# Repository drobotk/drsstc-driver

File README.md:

# DRSSTC driver

This is a KiCad project of the DRSSTC driver used in my tesla coil.

# Features:
- Single CT input for both clock and overcurrent detection
- Phase lead adjustable with a potentiometer, no need for a tunable inductor
- Adjustable self-oscillation, useful for testing and running a coil at the upper pole frequency
- Traditional / pulse skipping operation selectable with a jumper
- Adjustable UVLO for protecting precious IGBTs
- 74AHC high speed logic, less phase lead needed
- More modern parts than a UD2.7c

# Credits
As with most DRSSTC drivers, this one is based on previous work of many people (Steve Ward, Finn Hammer, Philip Slawinski, Bart Anderson, Eric Goodchild, Gao Guangyan, etc.). The design I took the most inspiration from is [this](https://highvoltageforum.net/index.php?topic=2054.0) project by [Mike](https://highvoltageforum.net/index.php?action=profile;u=1209) on HVF.

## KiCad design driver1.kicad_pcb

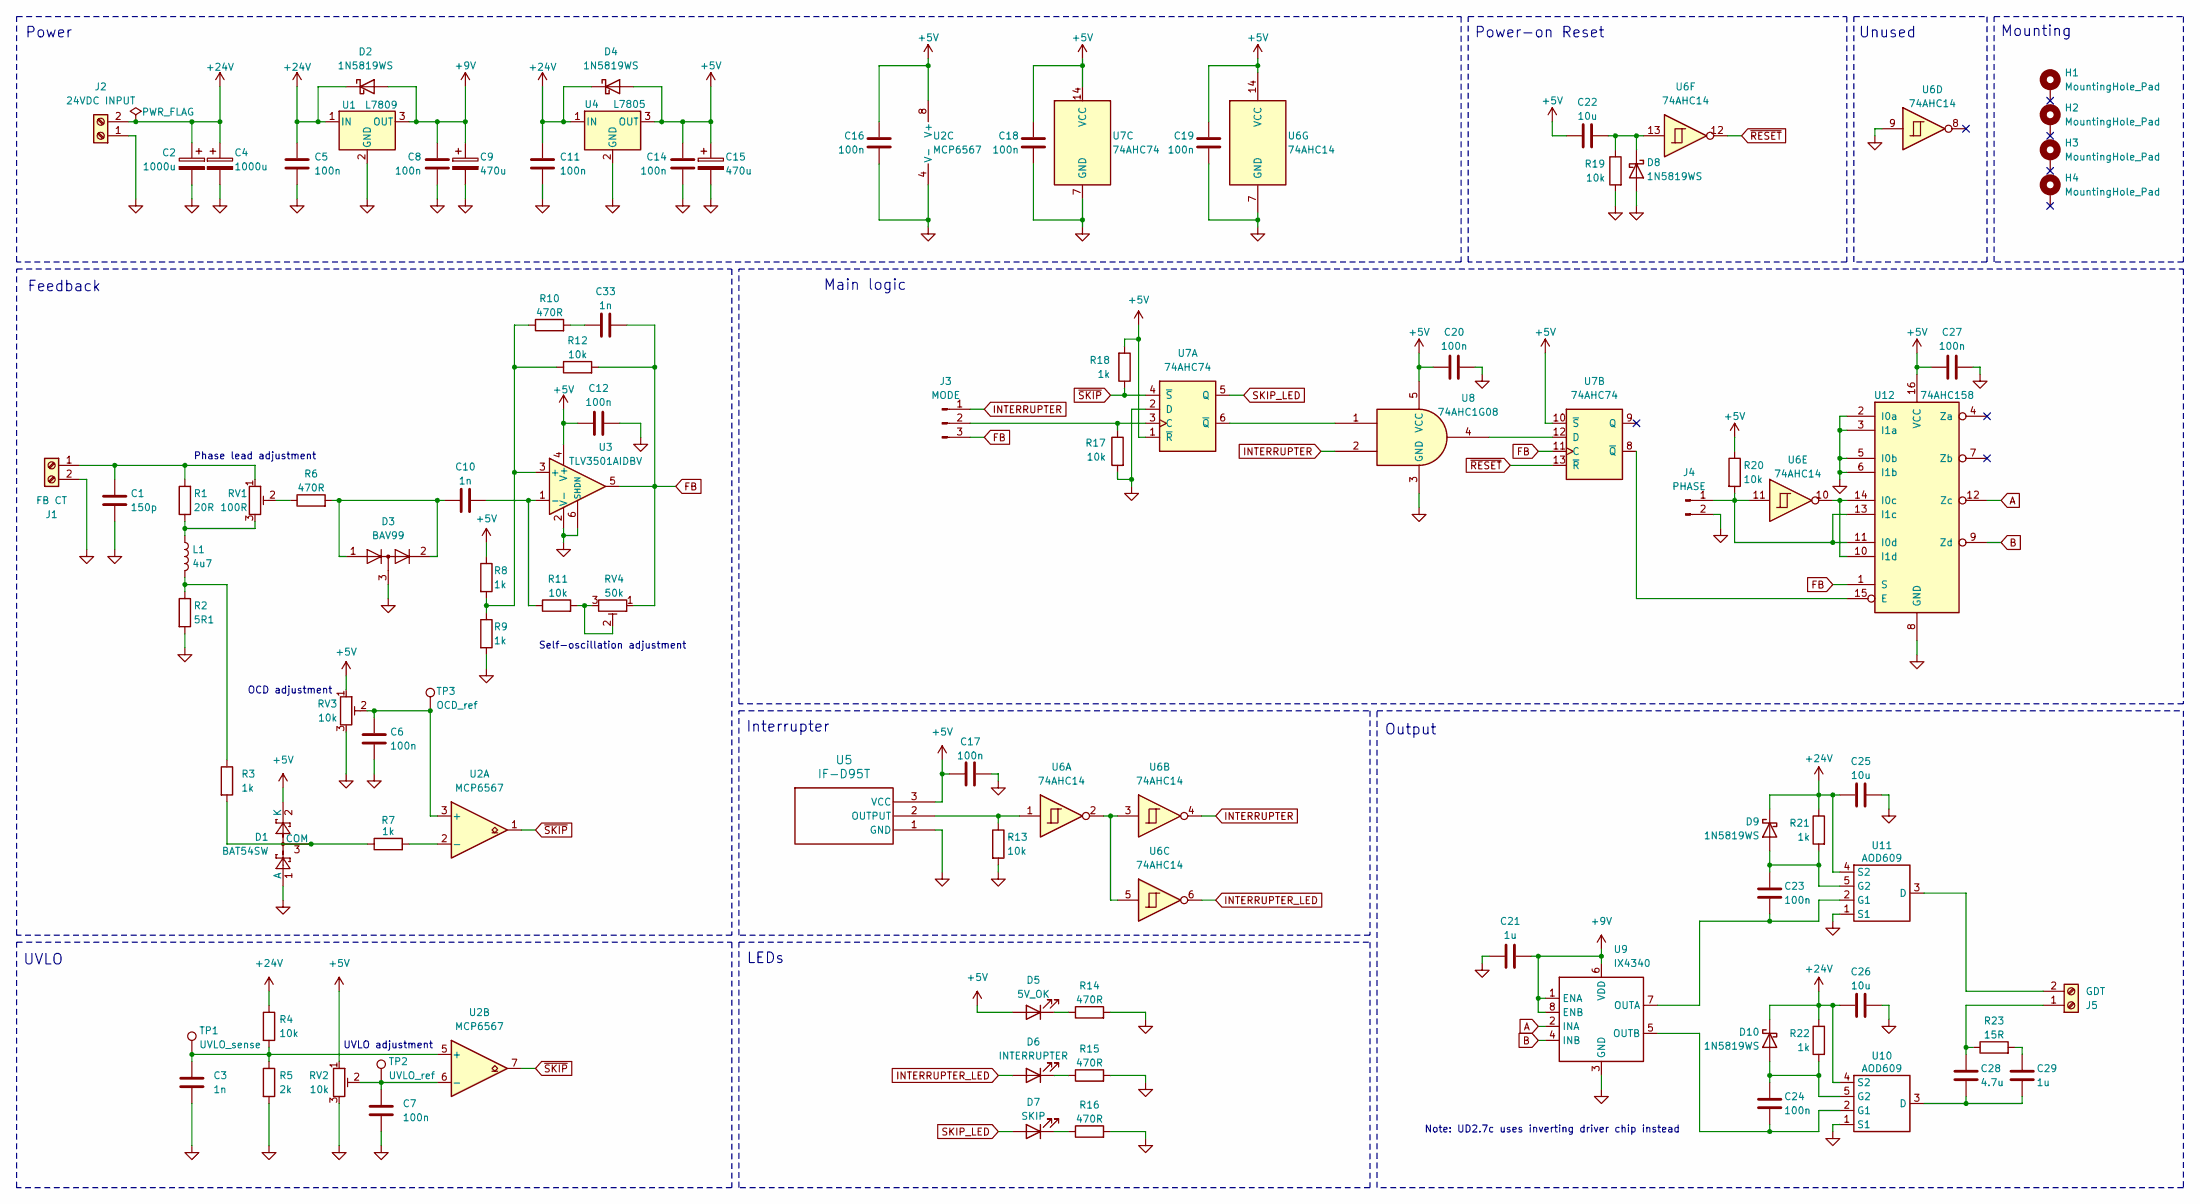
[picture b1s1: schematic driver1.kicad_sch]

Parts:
C1: 150p; C_0603_1608Metric_Pad1.08x0.95mm_HandSolder
C2, C4: 1000u; CP_Radial_D12.5mm_P5.00mm
C3, C10, C33: 1n; C_0603_1608Metric_Pad1.08x0.95mm_HandSolder
C5, C6, C7, C8, C11, C12, C14, C16, C17, C18, C19, C20, C27: 100n; C_0603_1608Metric_Pad1.08x0.95mm_HandSolder
C9, C15: 470u; CP_Radial_D8.0mm_P3.50mm
C21: 1u; C_0805_2012Metric_Pad1.18x1.45mm_HandSolder
C22, C25, C26: 10u; C_0805_2012Metric_Pad1.18x1.45mm_HandSolder
C23, C24: 100n; C_0805_2012Metric_Pad1.18x1.45mm_HandSolder
C28: 4.7u; C_1210_3225Metric_Pad1.33x2.70mm_HandSolder
C29: 1u; C_1210_3225Metric_Pad1.33x2.70mm_HandSolder
D1: BAT54SW; SOT-323_SC-70
D2, D4, D8, D9, D10: 1N5819WS; D_SOD-323
D3: BAV99; SOT-23
D5: 5V_OK; LED_D3.0mm
D6: INTERRUPTER; LED_D3.0mm
D7: SKIP; LED_D3.0mm
H1, H2, H3, H4: MountingHole_Pad; MountingHole_3.2mm_M3_Pad
J1: FB CT; Altech_AK100_1x02_P5.00mm
J2: 24VDC INPUT; Altech_AK100_1x02_P5.00mm
J3: MODE; PinHeader_1x03_P2.54mm_Vertical
J4: PHASE; PinHeader_1x02_P2.54mm_Vertical
J5: GDT; Altech_AK100_1x02_P5.00mm
L1: 4u7; L_Radial_D7.5mm_P3.50mm_Fastron_07P
R1: 20R; R_2512_6332Metric_Pad1.40x3.35mm_HandSolder
R2: 5R1; R_1210_3225Metric_Pad1.30x2.65mm_HandSolder
R3, R7, R8, R9, R18, R21, R22: 1k; R_0603_1608Metric_Pad0.98x0.95mm_HandSolder
R4, R11, R12, R13, R17, R19, R20: 10k; R_0603_1608Metric_Pad0.98x0.95mm_HandSolder
R5: 2k; R_0603_1608Metric_Pad0.98x0.95mm_HandSolder
R6, R10, R14, R15, R16: 470R; R_0603_1608Metric_Pad0.98x0.95mm_HandSolder
R23: 15R; R_1210_3225Metric_Pad1.30x2.65mm_HandSolder
RV1: 100R; Potentiometer_Bourns_3296W_Vertical
RV2, RV3: 10k; Potentiometer_Bourns_3296W_Vertical
RV4: 50k; Potentiometer_Bourns_3296W_Vertical
TP1: UVLO_sense; TestPoint_Pad_D2.0mm
TP2: UVLO_ref; TestPoint_Pad_D2.0mm
TP3: OCD_ref; TestPoint_Pad_D2.0mm
U1: L7809; TO-252-2
U2: MCP6567; MSOP-8_3x3mm_P0.65mm
U3: TLV3501AIDBV; SOT-23-6
U4: L7805; TO-252-2
U5: IF-D95T; IF-D95T_IFB
U6: 74AHC14; TSSOP-14_4.4x5mm_P0.65mm
U7: 74AHC74; TSSOP-14_4.4x5mm_P0.65mm
U8: 74AHC1G08; SOT-353_SC-70-5
U9: IX4340; SOIC-8_3.9x4.9mm_P1.27mm
U10, U11: AOD609; TO-252-4
U12: 74AHC158; TSSOP-16_4.4x5mm_P0.65mm

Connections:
+5V: C12.2, C14.1, C15.1, C16.2, C17.1, C18.2, C19.2, C20.1, C22.1, C27.1, D1.2 (K), D4.2 (A), D5.2 (A), R8.1, R18.2, R20.1, RV2.1, RV3.1, U2.8 (V+), U3.4 (V+), U4.3 (OUT), U5.3 (VCC), U6.14 (VCC), U7.1 (~R), U7.10 (~S), U7.14 (VCC), U8.5 (VCC), U12.16 (VCC)
+9V: C8.1, C9.1, C21.2, D2.2 (A), U1.3 (OUT), U9.1 (ENA), U9.6 (VDD), U9.8 (ENB)
+24V: C2.1, C4.1, C5.1, C11.1, C25.1, C26.1, D2.1 (K), D4.1 (K), D9.1 (K), D10.1 (K), J2.2, R4.1, R21.1, R22.1, U1.1 (IN), U4.1 (IN), U10.4 (S2), U11.4 (S2)
A: U9.2 (INA), U12.12 (Zc)
B: U9.4 (INB), U12.9 (Zd)
FB: C33.2, J3.3, R12.2, RV4.1, U3.5, U7.11 (C), U12.1 (S)
GND: C1.2, C2.2, C3.2, C4.2, C5.2, C6.2, C7.2, C8.2, C9.2, C11.2, C12.1, C14.2, C15.2, C16.1, C17.2, C18.1, C19.1, C20.2, C21.1, C25.2, C26.2, C27.2, D1.1 (A), D3.3 (K), D8.2 (A), J1.2, J2.1, J4.2, R2.2, R5.2, R9.2, R13.2, R14.2, R15.2, R16.2, R17.2, R19.2, RV2.3, RV3.3, U1.2 (GND), U2.4 (V-), U3.2 (V-), U3.6 (SHDN), U4.2 (GND), U5.1 (GND), U6.7 (GND), U6.9, U7.2 (D), U7.7 (GND), U8.3 (GND), U9.3 (GND), U10.1 (S1), U11.1 (S1), U12.2 (I0a), U12.3 (I1a), U12.5 (I0b), U12.6 (I1b), U12.8 (GND)
INTERRUPTER: J3.1, U6.4, U8.2
INTERRUPTER_LED: D6.2 (A), U6.6
unnamed: C29.1, R23.2
unnamed: C33.1, R10.2
unnamed: D1.3 (COM), R3.2, R7.1
unnamed: C10.1, D3.1 (K), D3.2 (A), R6.2
unnamed: D5.1 (K), R14.1
unnamed: D6.1 (K), R15.1
unnamed: D7.1 (K), R16.1
unnamed: C22.2, D8.1 (K), R19.1, U6.13
unnamed: C23.1, D9.2 (A), R21.2, U11.5 (G2)
unnamed: C24.1, D10.2 (A), R22.2, U10.5 (G2)
unnamed: C1.1, J1.1, R1.2, RV1.1
unnamed: J3.2, R17.1, U7.3 (C)
unnamed: J4.1, R20.2, U6.11, U12.11 (I0d), U12.13 (I1c)
unnamed: C28.1, J5.1, R23.1
unnamed: J5.2, U11.3 (D)
unnamed: L1.1, R1.1, RV1.3
unnamed: L1.2, R2.1, R3.1
unnamed: R6.1, RV1.2
unnamed: R11.2, RV4.2, RV4.3
unnamed: C6.1, RV3.2, TP3.1 (1_1), U2.3 (+)
unnamed: R7.2, U2.2 (-)
unnamed: C3.1, R4.2, R5.1, TP1.1 (1_1), U2.5 (+)
unnamed: C7.1, RV2.2, TP2.1 (1_1), U2.6 (-)
unnamed: R8.2, R9.1, R10.1, R12.1, U3.3 (+)
unnamed: C10.2, R11.1, U3.1 (-)
unnamed: R13.1, U5.2 (OUTPUT), U6.1
unnamed: U6.2, U6.3, U6.5
unnamed: U7.6 (~Q), U8.1
unnamed: U7.12 (D), U8.4
unnamed: C28.2, C29.2, U10.3 (D)
unnamed: C24.2, U9.5 (OUTB), U10.2 (G1)
unnamed: C23.2, U9.7 (OUTA), U11.2 (G1)
unnamed: U7.8 (~Q), U12.15 (E)
unnamed: U6.10, U12.10 (I1d), U12.14 (I0c)
SKIP_LED: D7.2 (A), U7.5 (Q)
~RESET: U6.12, U7.13 (~R)
~SKIP: R18.1, U2.1, U2.7, U7.4 (~S)

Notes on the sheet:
Interrupter
Self-oscillation adjustment
Power
Unused
OCD adjustment
UVLO adjustment
UVLO
Power-on Reset
LEDs
Main logic
Phase lead adjustment
Note: UD2.7c uses inverting driver chip instead
Output
Feedback
Mounting

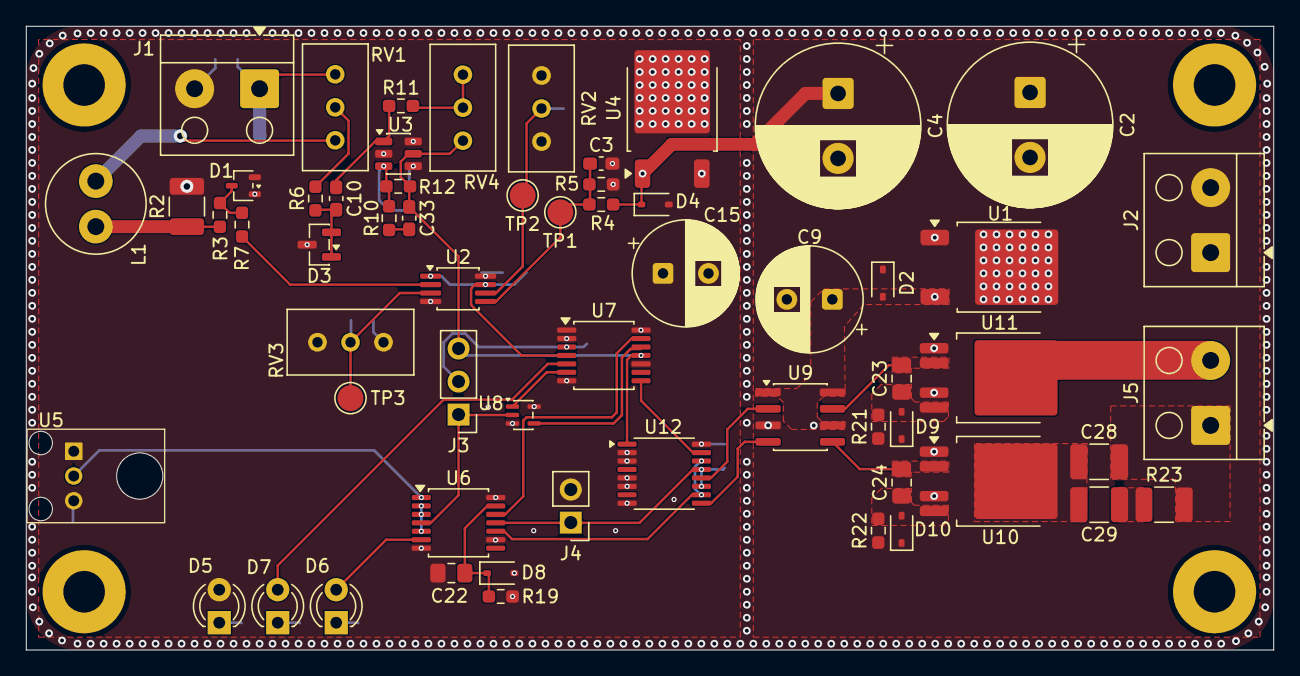
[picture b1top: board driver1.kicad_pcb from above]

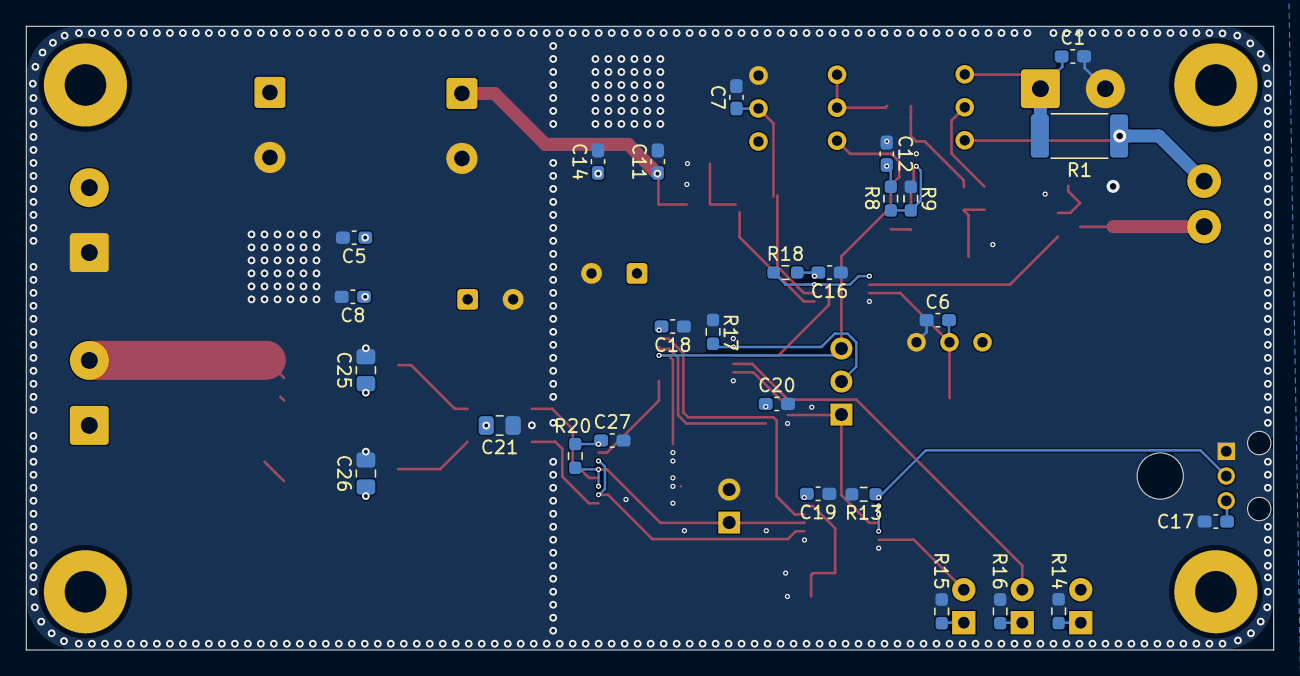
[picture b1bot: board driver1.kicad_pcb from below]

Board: 2 copper layers, 96.0 x 48.0 mm, 91 parts (27 on the bottom side), 46 nets.

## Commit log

2026-03-27 Create LICENSE
2026-03-27 Fix footprint link
2026-03-30 Progress
2026-04-01 pcb progress
2026-04-08 baby steps
2026-04-09 almost done
2026-04-09 infant steps
2026-04-10 the wheels on the bus go round and round
2026-04-14 i hate zones
2026-04-15 fix gitignore
